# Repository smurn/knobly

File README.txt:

Knobly - Avionics input device for flight simulators
====================================================

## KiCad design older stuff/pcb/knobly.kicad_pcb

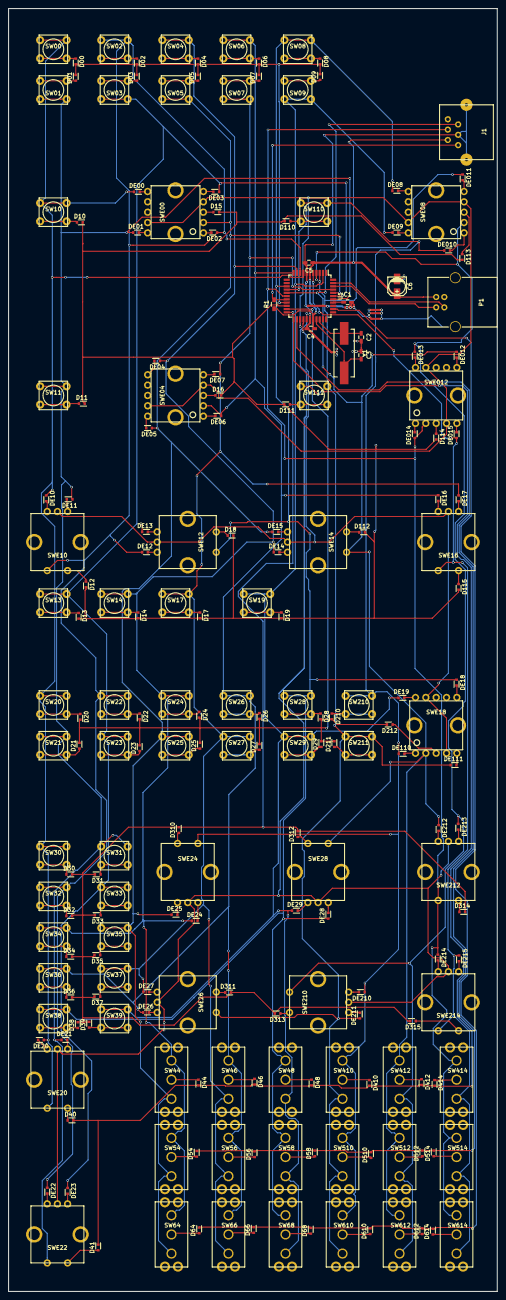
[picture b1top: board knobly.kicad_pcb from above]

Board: 2 copper layers, 120.0 x 315.0 mm, 205 parts (0 on the bottom side), 153 nets.

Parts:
C1: 470n; C_0603_HandSoldering
C2, C3: 15p; C_0603_HandSoldering
C4, C5: 100n; C_0603_HandSoldering
C6: 10u; c_elec_4x4.5
D00, D01, D02, D03, D04, D05, D06, D07, D08, D09, D10, D11, D12, D13, D14, D15, D16, D17, D18, D19, D20, D21, D22, D23, D24, D25, D26, D27, D28, D29, D30, D31, D32, D33, D34, D35, D36, D37, D38, D39, D40, D41, D44, D46, D48, D54, D56, D58, D64, D66, D68, D110, D111, D112, D113, D114, D115, D210, D211, D212, D310, D311, D312, D313, D314, D315, D410, D412, D414, D510, D512, D514, D610, D612, D614: D_Small; SOD-523
DE00, DE01, DE02, DE03, DE04, DE05, DE06, DE07, DE08, DE09, DE010, DE10, DE011, DE11, DE012, DE12, DE013, DE13, DE014, DE14, DE015, DE15, DE16, DE17, DE18, DE19, DE20, DE21, DE22, DE23, DE24, DE25, DE26, DE27, DE28, DE29, DE110, DE111, DE210, DE211, DE212, DE213, DE214, DE215: D_Small; SOD-523
J1: RJ12; RJ12_E
P1: USB_B
R1: 10k; R_0603_HandSoldering
SW00, SW01, SW02, SW03, SW04, SW05, SW06, SW07, SW08, SW09, SW10, SW11, SW13, SW14, SW17, SW19, SW20, SW21, SW22, SW23, SW24, SW25, SW26, SW27, SW28, SW29, SW30, SW31, SW32, SW33, SW34, SW35, SW36, SW37, SW38, SW39, SW110, SW111, SW210, SW211: TACT
SW44, SW46, SW48, SW54, SW56, SW58, SW64, SW66, SW68, SW410, SW412, SW414, SW510, SW512, SW514, SW610, SW612, SW614: FLIP; M2018ES2G13
SWE00, SWE04, SWE08, SWE012, SWE18: Concentric; e37
SWE10, SWE12, SWE14, SWE16, SWE20, SWE22, SWE24, SWE26, SWE28, SWE210, SWE212, SWE214: Encoder; pec11r
U1: PIC18F4550_TQFP; TQFP-44_10x10mm_Pitch0.8mm
Y1: 20Mhz; Crystal_HC49-SD_SMD

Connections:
COL0: DE00.2, DE10.2, DE20.2, SW00.1, SW10.1, SW20.1, SW30.1, SWE20.5, U1.8
COL1: DE01.2, DE11.2, DE21.2, SW01.1, SW11.1, SW21.1, SW31.1, SWE22.5, U1.38
COL2: DE02.2, DE12.2, DE22.2, SW02.1, SW22.1, SW32.1, SWE10.5, U1.9
COL3: DE03.2, DE13.2, DE23.2, SW03.1, SW13.1, SW23.1, SW33.1, U1.39
COL4: DE04.2, DE14.2, DE24.2, SW04.1, SW14.1, SW24.1, SW34.1, SW44.3, SW54.3, SW64.3, U1.10
COL5: DE05.2, DE15.2, DE25.2, SW05.1, SW25.1, SW35.1, SW44.1, SW54.1, SW64.1, SWE00.2, U1.40
COL6: DE06.2, DE16.2, DE26.2, SW06.1, SW26.1, SW36.1, SW46.3, SW56.3, SW66.3, SWE04.2, U1.11
COL7: DE07.2, DE17.2, DE27.2, SW07.1, SW17.1, SW27.1, SW37.1, SW46.1, SW56.1, SW66.1, U1.41
COL8: DE08.2, DE18.2, DE28.2, SW08.1, SW28.1, SW38.1, SW48.3, SW58.3, SW68.3, SWE12.5, U1.14
COL9: DE09.2, DE19.2, DE29.2, SW09.1, SW19.1, SW29.1, SW39.1, SW48.1, SW58.1, SW68.1, U1.2
COL10: DE010.2, DE110.2, DE210.2, SW110.1, SW210.1, SW410.3, SW510.3, SW610.3, SWE24.5, U1.15
COL11: DE011.2, DE111.2, DE211.2, SW111.1, SW211.1, SW410.1, SW510.1, SW610.1, SWE26.5, U1.3
COL12: DE012.2, DE212.2, J1.5, SW412.3, SW512.3, SW612.3, SWE14.5, SWE18.2, SWE28.5, U1.16
COL13: DE013.2, DE213.2, SW412.1, SW512.1, SW612.1, SWE08.2, SWE210.5, U1.4
COL14: DE014.2, DE214.2, J1.4, SW414.3, SW514.3, SW614.3, SWE012.2, SWE212.5, U1.17
COL15: DE015.2, DE215.2, SW414.1, SW514.1, SW614.1, SWE16.5, SWE214.5, U1.5
ENC0: SWE00.4, SWE00.9, SWE04.4, SWE04.9, SWE08.4, SWE08.9, SWE012.4, SWE012.9, U1.25
ENC1: SWE10.2, SWE12.2, SWE14.2, SWE16.2, SWE18.4, SWE18.9, U1.26
ENC2: SWE20.2, SWE22.2, SWE24.2, SWE26.2, SWE28.2, SWE210.2, SWE212.2, SWE214.2, U1.27
GND: C1.2, C2.2, C3.1, C4.2, C5.2, C6.2, J1.3, J1.7, J1.8, P1.4, P1.5, U1.7, U1.28
unnamed: C1.1, U1.37
unnamed: C2.1, U1.31, Y1.1
unnamed: C3.2, U1.30, Y1.2
unnamed: D00.2, SW00.2
unnamed: D01.2, SW01.2
unnamed: D02.2, SW02.2
unnamed: D03.2, SW03.2
unnamed: D04.2, SW04.2
unnamed: D05.2, SW05.2
unnamed: D06.2, SW06.2
unnamed: D07.2, SW07.2
unnamed: D08.2, SW08.2
unnamed: D09.2, SW09.2
unnamed: D10.2, SW10.2
unnamed: D11.2, SW11.2
unnamed: D12.2, SWE10.4
unnamed: D13.2, SW13.2
unnamed: D14.2, SW14.2
unnamed: D15.2, SWE00.3
unnamed: D16.2, SWE04.3
unnamed: D17.2, SW17.2
unnamed: D18.2, SWE12.4
unnamed: D19.2, SW19.2
unnamed: D20.2, SW20.2
unnamed: D21.2, SW21.2
unnamed: D22.2, SW22.2
unnamed: D23.2, SW23.2
unnamed: D24.2, SW24.2
unnamed: D25.2, SW25.2
unnamed: D26.2, SW26.2
unnamed: D27.2, SW27.2
unnamed: D28.2, SW28.2
unnamed: D29.2, SW29.2
unnamed: D30.2, SW30.2
unnamed: D31.2, SW31.2
unnamed: D32.2, SW32.2
unnamed: D33.2, SW33.2
unnamed: D34.2, SW34.2
unnamed: D35.2, SW35.2
unnamed: D36.2, SW36.2
unnamed: D37.2, SW37.2
unnamed: D38.2, SW38.2
unnamed: D39.2, SW39.2
unnamed: D40.2, SWE20.4
unnamed: D41.2, SWE22.4
unnamed: D44.2, SW44.2
unnamed: D46.2, SW46.2
unnamed: D48.2, SW48.2
unnamed: D54.2, SW54.2
unnamed: D56.2, SW56.2
unnamed: D58.2, SW58.2
unnamed: D64.2, SW64.2
unnamed: D66.2, SW66.2
unnamed: D68.2, SW68.2
unnamed: D110.2, SW110.2
unnamed: D111.2, SW111.2
unnamed: D112.2, SWE14.4
unnamed: D113.2, SWE08.3
unnamed: D114.2, SWE012.3
unnamed: D115.2, SWE16.4
unnamed: D210.2, SW210.2
unnamed: D211.2, SW211.2
unnamed: D212.2, SWE18.3
unnamed: D310.2, SWE24.4
unnamed: D311.2, SWE26.4
unnamed: D312.2, SWE28.4
unnamed: D313.2, SWE210.4
unnamed: D314.2, SWE212.4
unnamed: D315.2, SWE214.4
unnamed: D410.2, SW410.2
unnamed: D412.2, SW412.2
unnamed: D414.2, SW414.2
unnamed: D510.2, SW510.2
unnamed: D512.2, SW512.2
unnamed: D514.2, SW514.2
unnamed: D610.2, SW610.2
unnamed: D612.2, SW612.2
unnamed: D614.2, SW614.2
unnamed: DE00.1, SWE00.6
unnamed: DE01.1, SWE00.10
unnamed: DE02.1, SWE00.1
unnamed: DE03.1, SWE00.5
unnamed: DE04.1, SWE04.6
unnamed: DE05.1, SWE04.10
unnamed: DE06.1, SWE04.1
unnamed: DE07.1, SWE04.5
unnamed: DE08.1, SWE08.6
unnamed: DE09.1, SWE08.10
unnamed: DE010.1, SWE08.1
unnamed: DE10.1, SWE10.3
unnamed: DE011.1, SWE08.5
unnamed: DE11.1, SWE10.1
unnamed: DE012.1, SWE012.6
unnamed: DE12.1, SWE12.3
unnamed: DE013.1, SWE012.10
unnamed: DE13.1, SWE12.1
unnamed: DE014.1, SWE012.1
unnamed: DE14.1, SWE14.3
unnamed: DE015.1, SWE012.5
unnamed: DE15.1, SWE14.1
unnamed: DE16.1, SWE16.3
unnamed: DE17.1, SWE16.1
unnamed: DE18.1, SWE18.6
unnamed: DE19.1, SWE18.10
unnamed: DE20.1, SWE20.3
unnamed: DE21.1, SWE20.1
unnamed: DE22.1, SWE22.3
unnamed: DE23.1, SWE22.1
unnamed: DE24.1, SWE24.3
unnamed: DE25.1, SWE24.1
unnamed: DE26.1, SWE26.3
unnamed: DE27.1, SWE26.1
unnamed: DE28.1, SWE28.3
unnamed: DE29.1, SWE28.1
unnamed: DE110.1, SWE18.1
unnamed: DE111.1, SWE18.5
unnamed: DE210.1, SWE210.3
unnamed: DE211.1, SWE210.1
unnamed: DE212.1, SWE212.3
unnamed: DE213.1, SWE212.1
unnamed: DE214.1, SWE214.3
unnamed: DE215.1, SWE214.1
unnamed: J1.1, R1.2, U1.18
unnamed: P1.2, U1.42
unnamed: P1.3, U1.43
ROW0: D00.1, D01.1, D02.1, D03.1, D04.1, D05.1, D06.1, D07.1, D08.1, D09.1, U1.19
ROW1: D10.1, D11.1, D12.1, D13.1, D14.1, D15.1, D16.1, D17.1, D18.1, D19.1, D110.1, D111.1, D112.1, D113.1, D114.1, D115.1, U1.20
ROW2: D20.1, D21.1, D22.1, D23.1, D24.1, D25.1, D26.1, D27.1, D28.1, D29.1, D210.1, D211.1, D212.1, U1.21
ROW3: D30.1, D31.1, D32.1, D33.1, D34.1, D35.1, D36.1, D37.1, D38.1, D39.1, D310.1, D311.1, D312.1, D313.1, D314.1, D315.1, U1.22
ROW4: D40.1, D41.1, D44.1, D46.1, D48.1, D410.1, D412.1, D414.1, U1.23
ROW5: D54.1, D56.1, D58.1, D510.1, D512.1, D514.1, U1.24
ROW6: D64.1, D66.1, D68.1, D610.1, D612.1, D614.1, U1.35
VCC: C4.1, C5.1, C6.1, J1.2, P1.1, R1.1, U1.6, U1.29

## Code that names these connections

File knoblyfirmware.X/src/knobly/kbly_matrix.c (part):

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    CMCON = 0x07;   // Disable comparators (RA0-3) 

    // Configure Port A
    TRISAbits.TRISA0 = 0;   // Row0
    TRISAbits.TRISA1 = 0;   // Row1
    TRISAbits.TRISA2 = 0;   // Row2
    TRISAbits.TRISA3 = 0;   // Row3
    TRISAbits.TRISA4 = 0;   // Row4
    TRISAbits.TRISA5 = 0;   // Row5
    LATA = 0xFF;
    
    // Configure PORT B
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    INTCON2bits.RBPU = 0;   // Enable pull-ups
    
    // Configure Port C
    TRISCbits.TRISC1 = 0;   // Row6
    TRISCbits.TRISC6 = 0;   // debug output
    LATCbits.LATC1 = 1;
    
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    PORTEbits.RDPU = 1;     // Enable pull-ups

    // Configure Port E
    TRISEbits.TRISE0 = 0;   // Enc0
    TRISEbits.TRISE1 = 0;   // Enc1
    TRISEbits.TRISE2 = 0;   // Enc2
    LATEbits.LATE0 = 1;
    LATEbits.LATE1 = 1;
    LATEbits.LATE2 = 1;
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            
            kblyhid_joystick0.a = debounce_btn_group(raw_a, kblyhid_joystick0.a, 0, &kblyhid_js0_dirty);
            kblyhid_joystick0.b = debounce_btn_group(raw_b, kblyhid_joystick0.b, 1, &kblyhid_js0_dirty);
            LATAbits.LATA0 = 1; // Disable Row0
            LATEbits.LATE0 = 0; // Enable Enc0
            break;

        case 1: // enc0
            encoder(raw_a, raw_b, 0xFF, 0, &kblyhid_joystick3.c, &kblyhid_joystick3.d, &kblyhid_js3_dirty);
            LATEbits.LATE0 = 1; // Disable Enc0
            LATEbits.LATE1 = 0; // Enable Enc1
            break;

        case 2: // enc1
            encoder(raw_a, raw_b, 0x30, 1, &kblyhid_joystick4.a, &kblyhid_joystick4.b, &kblyhid_js4_dirty);
            LATEbits.LATE1 = 1; // Disable Enc1
            LATEbits.LATE2 = 0; // Enable Enc2
            break;

        case 3: // enc2
            encoder(raw_a, raw_b, 0xFC, 2, &kblyhid_joystick4.c, &kblyhid_joystick4.d, &kblyhid_js4_dirty);
            LATEbits.LATE2 = 1; // Disable Enc2
            LATAbits.LATA1 = 0; // Enable Row1
            break;

        case 4: // row1
            kblyhid_joystick0.c = debounce_btn_group(raw_a, kblyhid_joystick0.c, 2, &kblyhid_js0_dirty);
            kblyhid_joystick0.d = debounce_btn_group(raw_b, kblyhid_joystick0.d, 3, &kblyhid_js0_dirty);
            LATAbits.LATA1 = 1; // Disable Row1
            LATEbits.LATE0 = 0; // Enable Enc0
            break;

        case 5: // enc0
            encoder(raw_a, raw_b, 0xFF, 0, &kblyhid_joystick3.c, &kblyhid_joystick3.d, &kblyhid_js3_dirty);
            LATEbits.LATE0 = 1; // Disable Enc0
            LATEbits.LATE1 = 0; // Enable Enc1
            break;

        case 6: // enc1
            encoder(raw_a, raw_b, 0x30, 1, &kblyhid_joystick4.a, &kblyhid_joystick4.b, &kblyhid_js4_dirty);
            LATEbits.LATE1 = 1; // Disable Enc1
            LATEbits.LATE2 = 0; // Enable Enc2
            break;

        case 7: // enc2
            encoder(raw_a, raw_b, 0xFC, 2, &kblyhid_joystick4.c, &kblyhid_joystick4.d, &kblyhid_js4_dirty);
            LATEbits.LATE2 = 1; // Disable Enc2
            LATAbits.LATA2 = 0; // Enable Row2
            break;

        case 8: // row2
            kblyhid_joystick1.a = debounce_btn_group(raw_a, kblyhid_joystick1.a, 4, &kblyhid_js1_dirty);
            kblyhid_joystick1.b = debounce_btn_group(raw_b, kblyhid_joystick1.b, 5, &kblyhid_js1_dirty);
            LATAbits.LATA2 = 1; // Disable Row2
            LATEbits.LATE0 = 0; // Enable Enc0
            break;

        case 9: // enc0
            encoder(raw_a, raw_b, 0xFF, 0, &kblyhid_joystick3.c, &kblyhid_joystick3.d, &kblyhid_js3_dirty);
            LATEbits.LATE0 = 1; // Disable Enc0
            LATEbits.LATE1 = 0; // Enable Enc1
            break;

        case 10: // enc1
            encoder(raw_a, raw_b, 0x30, 1, &kblyhid_joystick4.a, &kblyhid_joystick4.b, &kblyhid_js4_dirty);
            LATEbits.LATE1 = 1; // Disable Enc1
            LATEbits.LATE2 = 0; // Enable Enc2
            break;

        case 11: // enc2
            encoder(raw_a, raw_b, 0xFC, 2, &kblyhid_joystick4.c, &kblyhid_joystick4.d, &kblyhid_js4_dirty);
            LATEbits.LATE2 = 1; // Disable Enc2
            LATAbits.LATA3 = 0; // Enable Row3
            break;

        case 12: // row3
            kblyhid_joystick1.c = debounce_btn_group(raw_a, kblyhid_joystick1.c, 6, &kblyhid_js1_dirty);
            kblyhid_joystick1.d = debounce_btn_group(raw_b, kblyhid_joystick1.d, 7, &kblyhid_js1_dirty);
            LATAbits.LATA3 = 1; // Disable Row3
            LATEbits.LATE0 = 0; // Enable Enc0
            break;

        case 13: // enc0
            encoder(raw_a, raw_b, 0xFF, 0, &kblyhid_joystick3.c, &kblyhid_joystick3.d, &kblyhid_js3_dirty);
            LATEbits.LATE0 = 1; // Disable Enc0
            LATEbits.LATE1 = 0; // Enable Enc1
            break;

        case 14: // enc1
            encoder(raw_a, raw_b, 0x30, 1, &kblyhid_joystick4.a, &kblyhid_joystick4.b, &kblyhid_js4_dirty);
            LATEbits.LATE1 = 1; // Disable Enc1
            LATEbits.LATE2 = 0; // Enable Enc2
            break;

        case 15: // enc2
            encoder(raw_a, raw_b, 0xFC, 2, &kblyhid_joystick4.c, &kblyhid_joystick4.d, &kblyhid_js4_dirty);
            LATEbits.LATE2 = 1; // Disable Enc2
            LATAbits.LATA4 = 0; // Enable Row4
            break;

        case 16: // row4
            kblyhid_joystick2.a = debounce_btn_group(raw_a, kblyhid_joystick2.a, 8, &kblyhid_js2_dirty);
            kblyhid_joystick2.b = debounce_btn_group(raw_b, kblyhid_joystick2.b, 9, &kblyhid_js2_dirty);
            LATAbits.LATA4 = 1; // Disable Row4
            LATEbits.LATE0 = 0; // Enable Enc0
            break;

        case 17: // enc0
            encoder(raw_a, raw_b, 0xFF, 0, &kblyhid_joystick3.c, &kblyhid_joystick3.d, &kblyhid_js3_dirty);
            LATEbits.LATE0 = 1; // Disable Enc0
            LATEbits.LATE1 = 0; // Enable Enc1
            break;

        case 18: // enc1
            encoder(raw_a, raw_b, 0x30, 1, &kblyhid_joystick4.a, &kblyhid_joystick4.b, &kblyhid_js4_dirty);
            LATEbits.LATE1 = 1; // Disable Enc1
            LATEbits.LATE2 = 0; // Enable Enc2
            break;

        case 19: // enc2
            encoder(raw_a, raw_b, 0xFC, 2, &kblyhid_joystick4.c, &kblyhid_joystick4.d, &kblyhid_js4_dirty);
            LATEbits.LATE2 = 1; // Disable Enc2
            LATAbits.LATA5 = 0; // Enable Row5
            break;

        case 20: // row5
            kblyhid_joystick2.c = debounce_btn_group(raw_a, kblyhid_joystick2.c, 10, &kblyhid_js2_dirty);
            kblyhid_joystick2.d = debounce_btn_group(raw_b, kblyhid_joystick2.d, 11, &kblyhid_js2_dirty);
            LATAbits.LATA5 = 1; // Disable Row5
            LATEbits.LATE0 = 0; // Enable Enc0
            break;

        case 21: // enc0
            encoder(raw_a, raw_b, 0xFF, 0, &kblyhid_joystick3.c, &kblyhid_joystick3.d, &kblyhid_js3_dirty);
            LATEbits.LATE0 = 1; // Disable Enc0
            LATEbits.LATE1 = 0; // Enable Enc1
            break;

        case 22: // enc1
            encoder(raw_a, raw_b, 0x30, 1, &kblyhid_joystick4.a, &kblyhid_joystick4.b, &kblyhid_js4_dirty);
            LATEbits.LATE1 = 1; // Disable Enc1
            LATEbits.LATE2 = 0; // Enable Enc2
            break;

        case 23: // enc2
            encoder(raw_a, raw_b, 0xFC, 2, &kblyhid_joystick4.c, &kblyhid_joystick4.d, &kblyhid_js4_dirty);
            LATEbits.LATE2 = 1; // Disable Enc2
            LATCbits.LATC1 = 0; // Enable Row6
            break;

        case 24: // row6
            kblyhid_joystick3.a = debounce_btn_group(raw_a, kblyhid_joystick3.a, 12, &kblyhid_js3_dirty);
            kblyhid_joystick3.b = debounce_btn_group(raw_b, kblyhid_joystick3.b, 13, &kblyhid_js3_dirty);
            LATCbits.LATC1 = 1; // Disable Row6
            LATEbits.LATE0 = 0; // Enable Enc0
            break;

        case 25: // enc0
            encoder(raw_a, raw_b, 0xFF, 0, &kblyhid_joystick3.c, &kblyhid_joystick3.d, &kblyhid_js3_dirty);
            LATEbits.LATE0 = 1; // Disable Enc0
            LATEbits.LATE1 = 0; // Enable Enc1
            break;

        case 26: // enc1
            encoder(raw_a, raw_b, 0x30, 1, &kblyhid_joystick4.a, &kblyhid_joystick4.b, &kblyhid_js4_dirty);
            LATEbits.LATE1 = 1; // Disable Enc1
            LATEbits.LATE2 = 0; // Enable Enc2
            break;

        case 27: // enc2
            encoder(raw_a, raw_b, 0xFC, 2, &kblyhid_joystick4.c, &kblyhid_joystick4.d, &kblyhid_js4_dirty);
            LATEbits.LATE2 = 1; // Disable Enc2
            LATAbits.LATA0 = 0; // Enable Row0
            break;


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            kblyhid_joystick0.a = debounce_btn_group(raw_a, kblyhid_joystick0.a, 0);
            kblyhid_joystick0.b = debounce_btn_group(raw_b, kblyhid_joystick0.b, 1);
            
            LATAbits.LATA0 = 1; // Disable Row0
            LATAbits.LATA1 = 0; // Enable Row1
            break;
        case 1: // Row1
            kblyhid_joystick0.c = debounce_btn_group(raw_a, kblyhid_joystick0.c, 2);
            kblyhid_joystick0.d = debounce_btn_group(raw_b, kblyhid_joystick0.d, 3);
            
            LATAbits.LATA1 = 1; // Disable Row1
            LATAbits.LATA2 = 0; // Enable Row2
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
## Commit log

2017-12-11 Reduced the rate at which HID reports are sent to host.
2017-12-11 Adding kicad project for PCB and frontpanel.
2017-12-11 Added 3d models
2017-12-12 License and pics.
2018-01-06 Fix bug that caused knobly to freeze after a few minutes.
2018-04-22 older stuff

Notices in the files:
knoblyfirmware.X/src/knobly/kbly_matrix.c:
Licensed to the Apache Software Foundation (ASF) under one
to you under the Apache License, Version 2.0 (the
